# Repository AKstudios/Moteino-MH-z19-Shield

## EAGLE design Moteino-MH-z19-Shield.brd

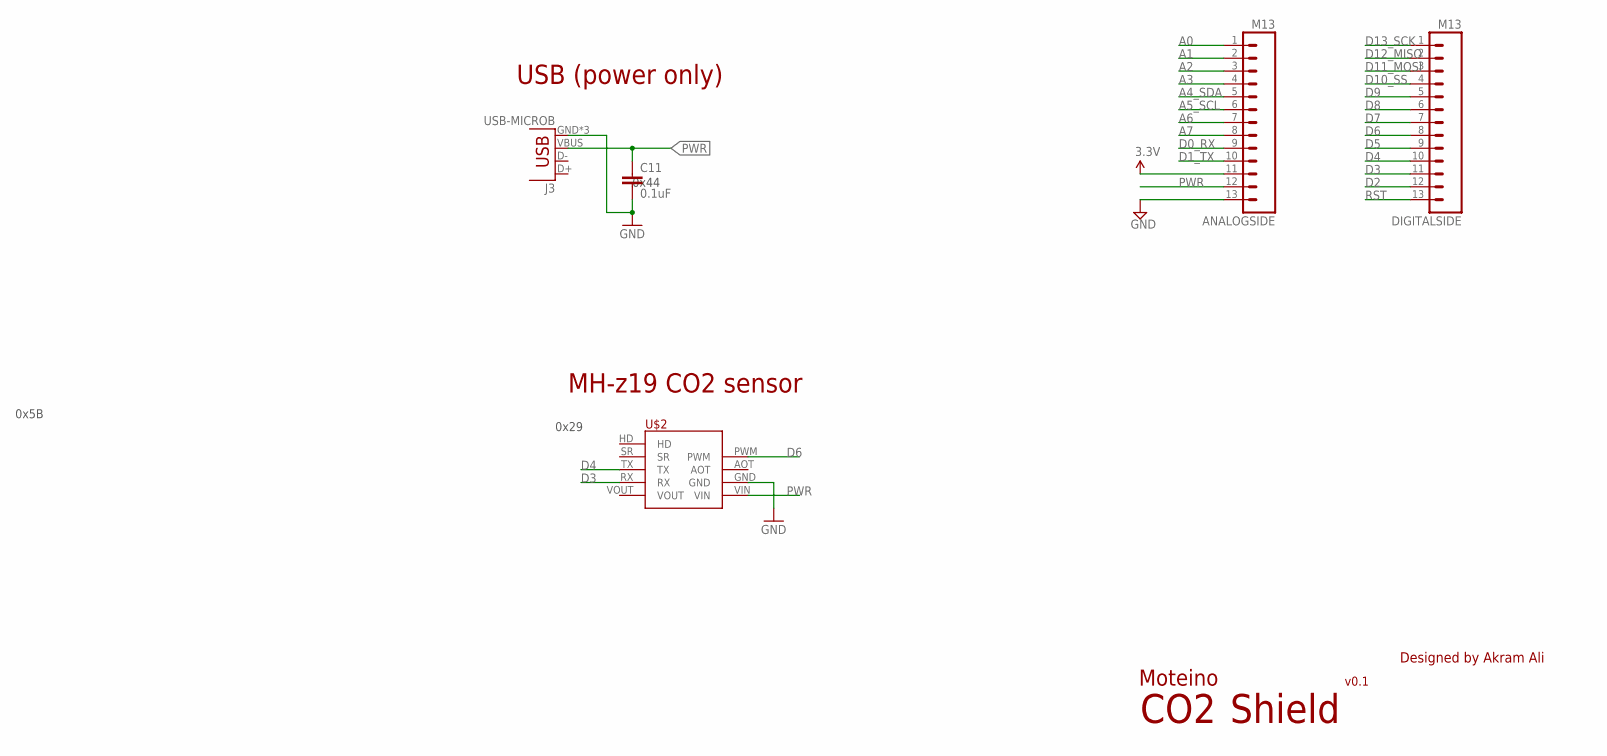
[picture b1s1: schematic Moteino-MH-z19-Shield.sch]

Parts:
ANALOGSIDE: M13; 1X13
C11: 0.1uF; 0805; MPN CC0805KRX7R9BB104
DIGITALSIDE: M13; 1X13
J3: USB-MICROB; MPN 47346-0001
U$2: MH-Z19

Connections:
A0: ANALOGSIDE.1
A1: ANALOGSIDE.2
A2: ANALOGSIDE.3
A3: ANALOGSIDE.4
A4_SDA: ANALOGSIDE.5
A5_SCL: ANALOGSIDE.6
A6: ANALOGSIDE.7
A7: ANALOGSIDE.8
D0_RX: ANALOGSIDE.9
D1_TX: ANALOGSIDE.10
D2: DIGITALSIDE.12
D3: DIGITALSIDE.11, U$2.RX
D4: DIGITALSIDE.10, U$2.TX
D5: DIGITALSIDE.9
D6: DIGITALSIDE.8, U$2.PWM
D7: DIGITALSIDE.7
D8: DIGITALSIDE.6
D9: DIGITALSIDE.5
D10_SS: DIGITALSIDE.4
D11_MOSI: DIGITALSIDE.3
D12_MISO: DIGITALSIDE.2
D13_SCK: DIGITALSIDE.1
GND: ANALOGSIDE.13, C11.2, J3.GND, J3.MT1 (GND), J3.MT2 (GND), U$2.GND
PWR: ANALOGSIDE.12, C11.1, J3.VBUS, U$2.VIN
RST: DIGITALSIDE.13
VCC: ANALOGSIDE.11

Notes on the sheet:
Moteino
Designed by Akram Ali
CO2
0x44
0x29
USB (power only)
Shield
v0.1
0x5B
MH-z19 CO2 sensor

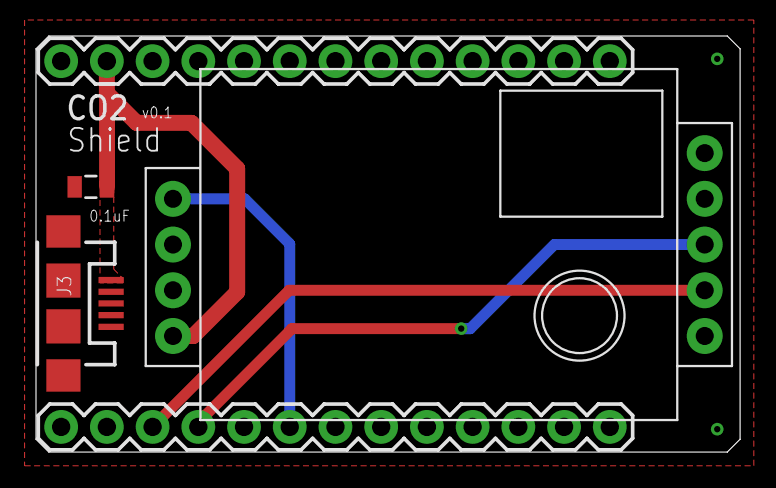
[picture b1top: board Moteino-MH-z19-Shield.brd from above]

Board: 2 copper layers, 39.1 x 23.1 mm, 5 parts (0 on the bottom side), 5 nets.

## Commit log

2017-06-09 :lollipop: Added .gitattributes & .gitignore files
2017-06-09 init
2017-06-23 Added firmware
2017-06-23 Added render
2020-07-04 firmware update
2020-07-04 added firmware v2
2020-07-04 firmware v2
2020-07-04 Rename Moteino_MH-z19.ino to Moteino_MH-z19_firmware_v1.ino
2020-07-04 changed folder name
2020-07-04 rename firmware

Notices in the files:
parts and their libraries:
SparkFun-Connectors: Licensing: CC v3.0 Share-Alike You are welcome to use this library for commercial purposes.
SparkFun-Capacitors: Licensing: Creative Commons ShareAlike 4.0 International - https://creativecommons.org/licenses/by-sa/4.0
